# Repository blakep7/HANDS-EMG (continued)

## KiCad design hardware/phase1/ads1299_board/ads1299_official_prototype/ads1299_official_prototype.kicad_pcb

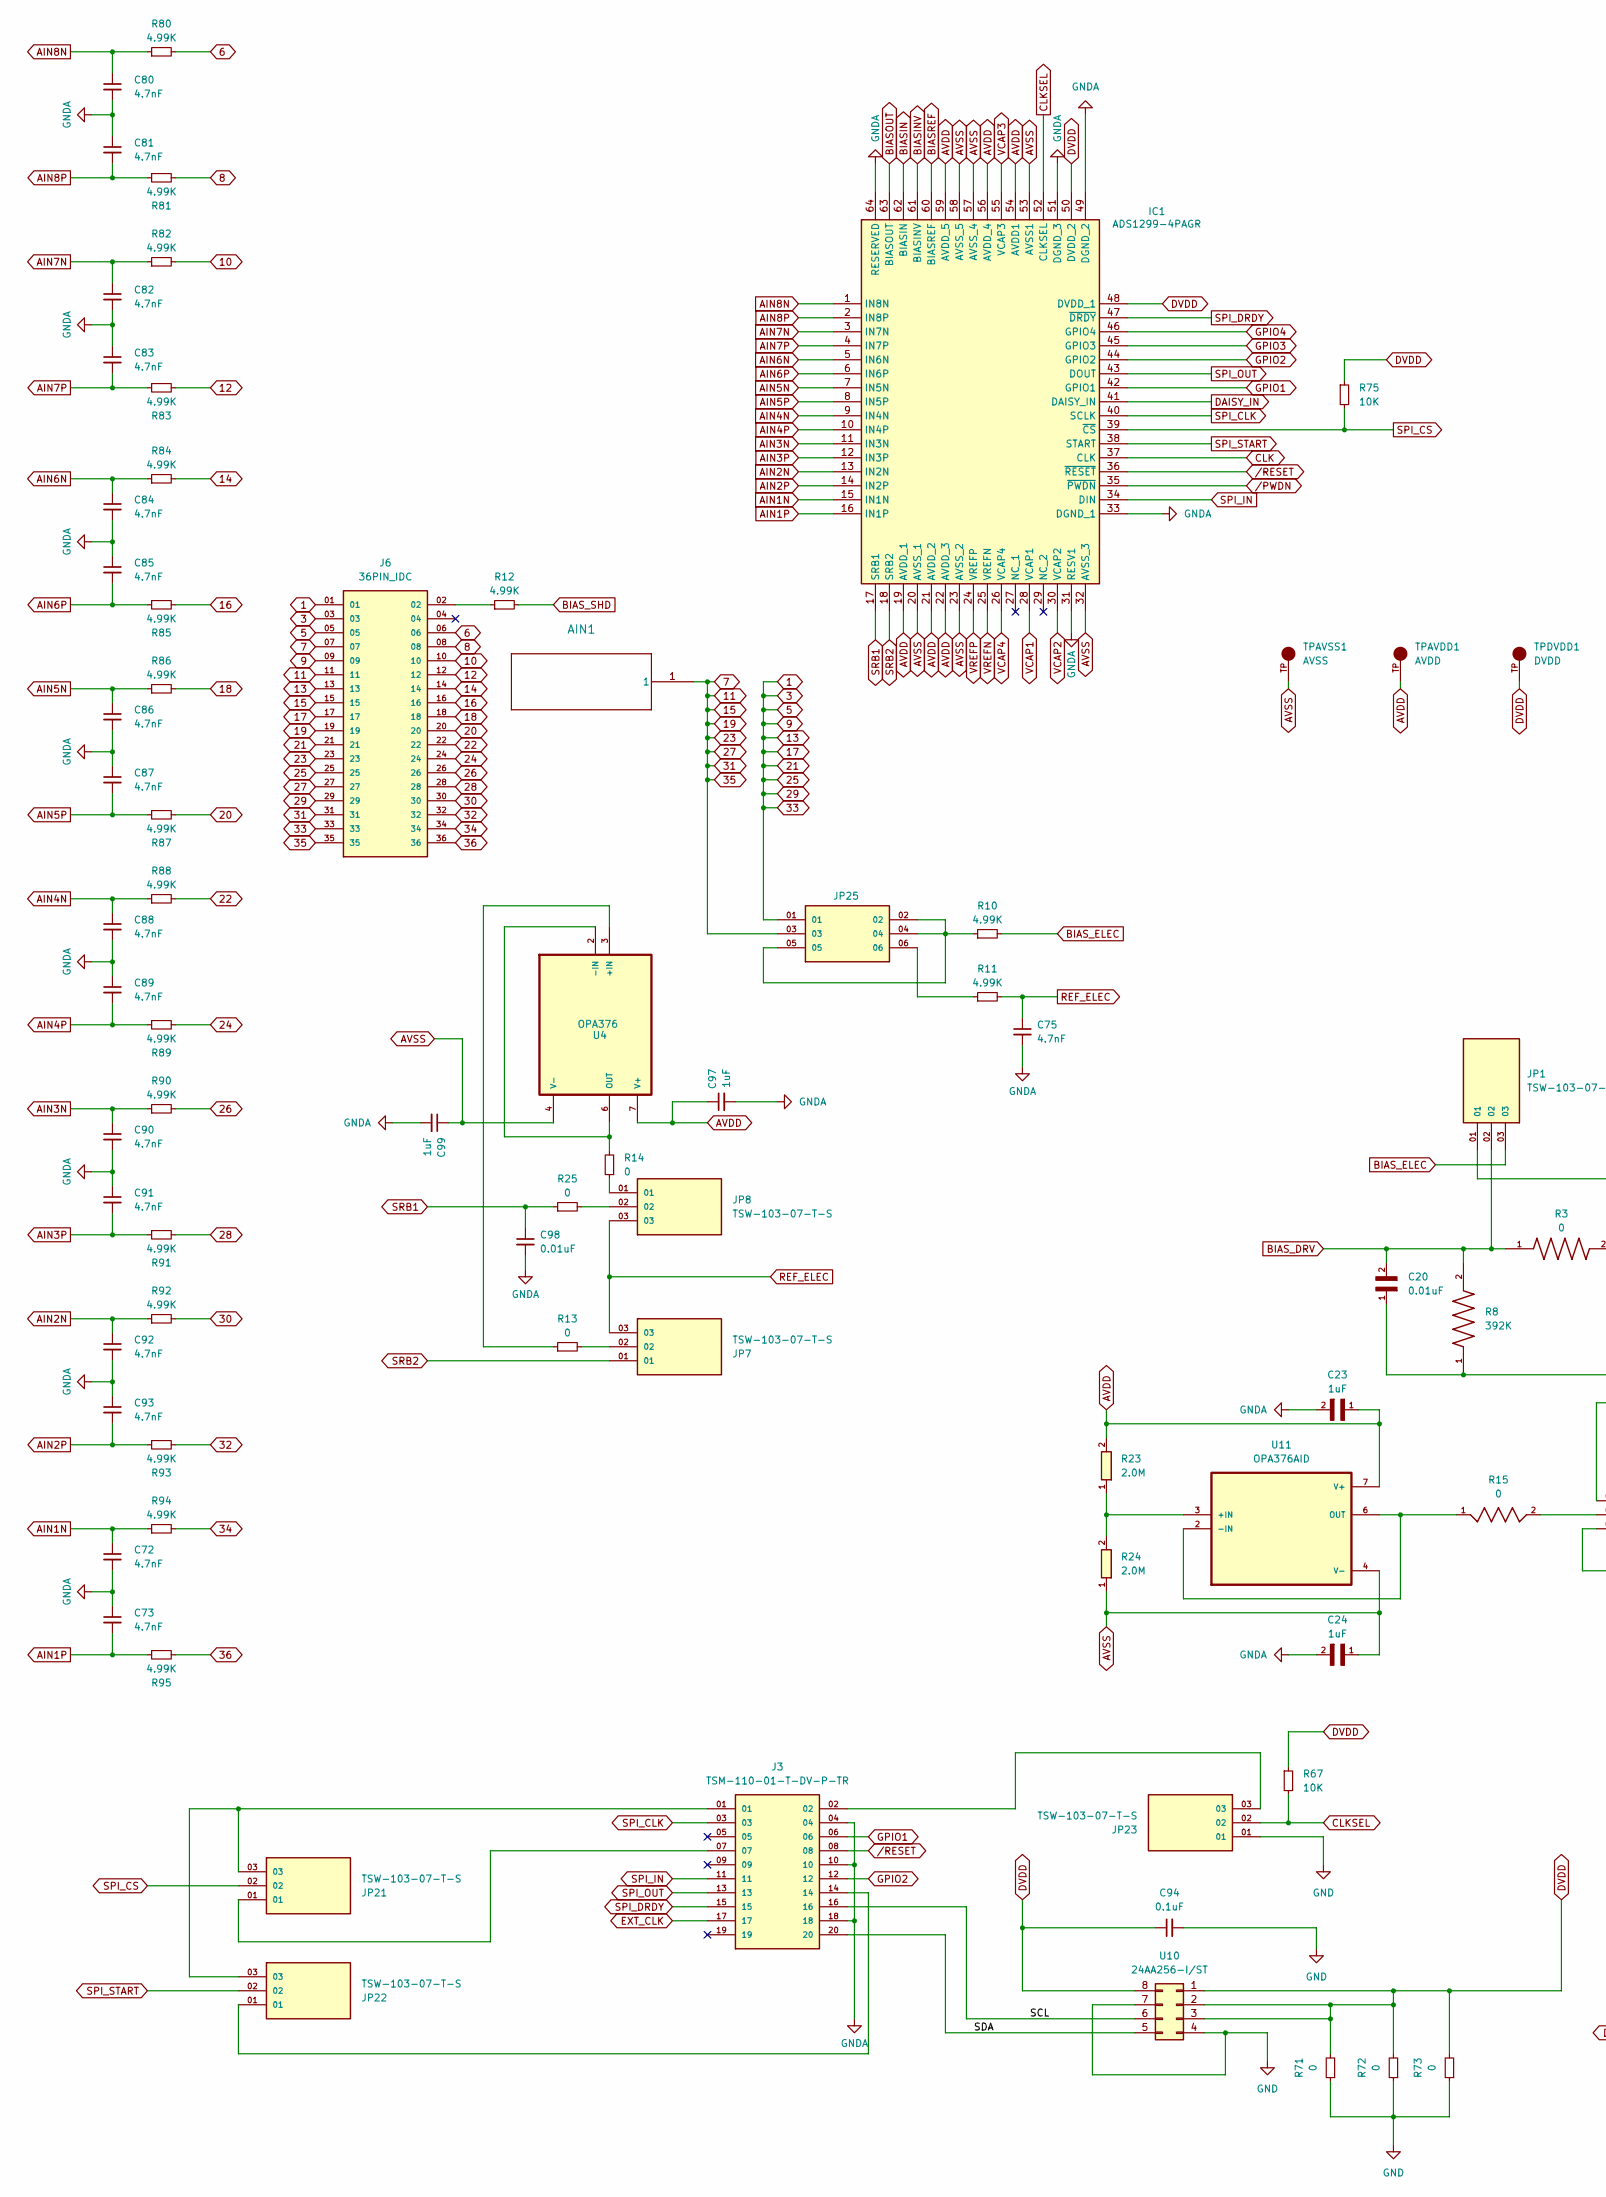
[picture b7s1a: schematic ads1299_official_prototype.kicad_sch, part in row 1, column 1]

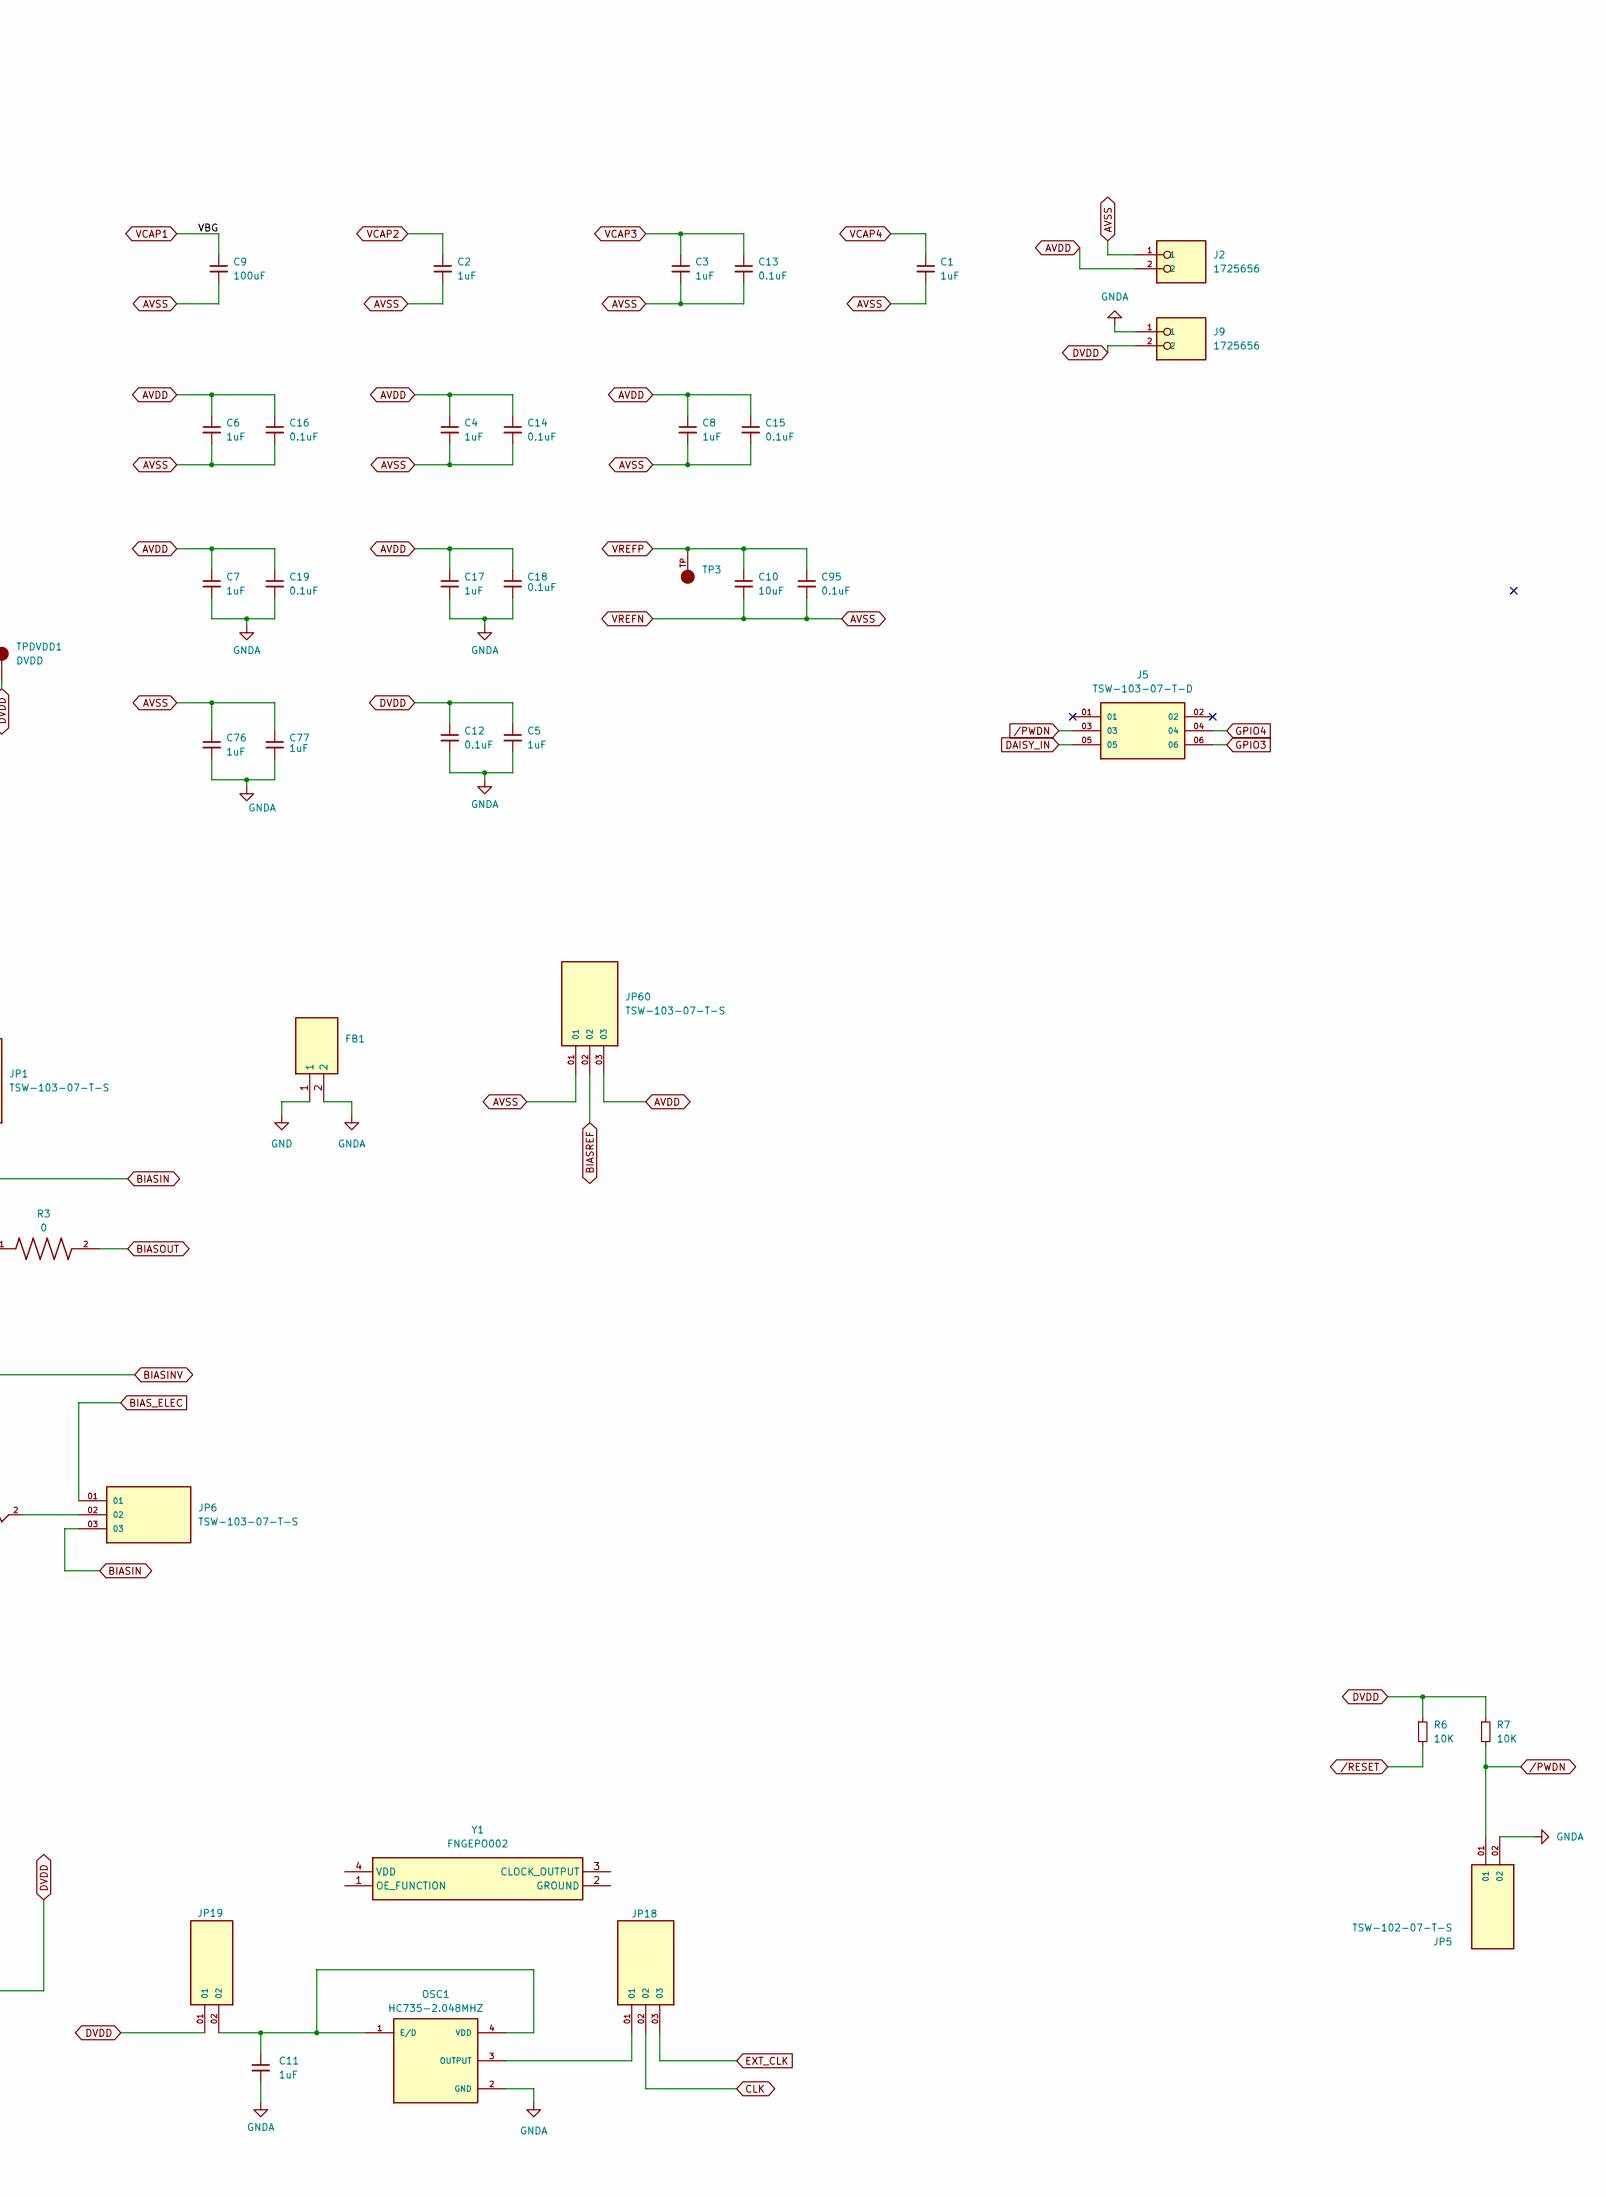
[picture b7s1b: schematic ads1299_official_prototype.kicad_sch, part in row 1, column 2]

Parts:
AIN1: AIN1; 132134_AMP
C1, C2, C3, C4, C5, C6, C7, C8, C11, C17, C23, C24, C76, C77, C97, C99: 1uF; CAPC1608X90N
C9: 100uF; CAPC3225X280N
C10: 10uF; CAPC2012X95N
C12, C13, C14, C15, C16, C18, C19, C94, C95: 0.1uF; CAPC1608X90N
C20, C98: 0.01uF; CAPC1608X90N
C72, C73, C75, C80, C81, C82, C83, C84, C85, C86, C87, C88, C89, C90, C91, C92, C93: 4.7nF; CAPC1608X90N
FB1: FCM_1608KF-601T03; BEADC1608X95N; Manufacturer_Part_Number FCM 1608KF-601T03
IC1: ADS1299-4PAGR; QFP50P1200X1200X120-64N; Manufacturer_Part_Number ADS1299-4PAGR; Mouser Part Number 595-ADS1299-4PAGR
J2, J9: 1725656; PHOENIX_1725656; PARTREV 03.03.2021
J3: TSM-110-01-T-DV-P-TR; SAMTEC_TSM-110-01-T-DV-P-TR
J5: TSW-103-07-T-D; SAMTEC_TSW-103-07-T-D; PARTREV R
J6: 36PIN_IDC; SAMTEC_SSW-118-21-F-D; PARTREV R
JP1, JP6, JP7, JP8, JP18, JP21, JP22, JP23, JP60: TSW-103-07-T-S; SAMTEC_TSW-103-07-T-S; PARTREV R
JP5, JP19: TSW-102-07-T-S; SAMTEC_TSW-102-07-T-S; PARTREV R
JP25: TSW-103-07-T-D; SAMTEC_TSW-103-07-T-D; PARTREV R
OSC1: HC735-2.048MHZ; XTAL_FXO-HC735-8; PARTREV 11/28/2007
R3, R25: 0; RESC1607X60N
R6, R7, R67, R75: 10K; RESC1607X60N
R8: 392K; RESC1608X55N
R10, R11, R12, R80, R81, R82, R83, R84, R85, R86, R87, R88, R89, R90, R91, R92, R93, R94, R95: 4.99K; RESC1608X60N
R13, R14, R15, R71, R72, R73: 0; RESC1005X40
R23, R24: 2.0M; 0603
TP3: 5000; KEYSTONE_5000; PARTREV H
TPAVDD1: AVDD; KEYSTONE_5000; PARTREV H
TPAVSS1: AVSS; KEYSTONE_5000; PARTREV H
TPDVDD1: DVDD; KEYSTONE_5000; PARTREV H
U4: OPA376; SOIC127P599X175-8N
U10: 24AA256-I/ST; SOP8P65_300X640X120L60X24N
U11: OPA376AID; SOIC127P599X175-8N
Y1: FNGEPO002; Manufacturer_Part_Number FNGEPO002; Mouser Part Number 729-FNGEPO002

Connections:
1: J6.01, J6.03, J6.05, J6.09, J6.13, J6.17, J6.21, J6.25, J6.29, J6.33, JP25.01
6: J6.06, R80.2
8: J6.08, R81.2
10: J6.10, R82.2
11: AIN1.1, J6.07, J6.11, J6.15, J6.19, J6.23, J6.27, J6.31, J6.35, JP25.03
12: J6.12, R83.2
14: J6.14, R84.2
16: J6.16, R85.2
18: J6.18, R86.2
20: J6.20, R87.2
22: J6.22, R88.2
24: J6.24, R89.2
26: J6.26, R90.2
28: J6.28, R91.2
30: J6.30, R92.2
32: J6.32, R93.2
34: J6.34, R94.2
36: J6.36, R95.2
/SCL: J3.16, U10.6
/SDA: J3.20, U10.5
AIN1N: C72.1, IC1.15 (IN1N), R94.1
AIN1P: C73.2, IC1.16 (IN1P), R95.1
AIN2N: C92.1, IC1.13 (IN2N), R92.1
AIN2P: C93.2, IC1.14 (IN2P), R93.1
AIN3N: C90.1, IC1.11 (IN3N), R90.1
AIN3P: C91.2, IC1.12 (IN3P), R91.1
AIN4N: C88.1, IC1.9 (IN4N), R88.1
AIN4P: C89.2, IC1.10 (IN4P), R89.1
AIN5N: C86.1, IC1.7 (IN5N), R86.1
AIN5P: C87.2, IC1.8 (IN5P), R87.1
AIN6N: C84.1, IC1.5 (IN6N), R84.1
AIN6P: C85.2, IC1.6 (IN6P), R85.1
AIN7N: C82.1, IC1.3 (IN7N), R82.1
AIN7P: C83.2, IC1.4 (IN7P), R83.1
AIN8N: C80.1, IC1.1 (IN8N), R80.1
AIN8P: C81.2, IC1.2 (IN8P), R81.1
AVDD: C4.1, C6.1, C7.1, C8.1, C14.1, C15.1, C16.1, C17.1, C18.1, C19.1, C23.1, C97.1, IC1.19 (AVDD_1), IC1.21 (AVDD_2), IC1.22 (AVDD_3), IC1.54 (AVDD1), IC1.56 (AVDD_4), IC1.59 (AVDD_5), J2.2, JP60.03, R23.2, TPAVDD1.TP, U4.7 (V+), U11.7 (V+)
AVSS: C1.2, C2.2, C3.2, C4.2, C6.2, C8.2, C9.2, C10.2, C13.2, C14.2, C15.2, C16.2, C24.1, C76.1, C77.1, C95.2, C99.1, IC1.20 (AVSS_1), IC1.23 (AVSS_2), IC1.25 (VREFN), IC1.32 (AVSS_3), IC1.53 (AVSS1), IC1.57 (AVSS_4), IC1.58 (AVSS_5), J2.1, JP60.01, R24.1, TPAVSS1.TP, U4.4 (V-), U11.4 (V-)
BIASIN: IC1.62 (BIASIN), JP1.01, JP6.03
BIASINV: C20.1, IC1.61 (BIASINV), R8.1
BIASOUT: IC1.63 (BIASOUT), R3.2
BIASREF: IC1.60 (BIASREF), JP60.02
BIAS_DRV: C20.2, JP1.02, R3.1, R8.2
BIAS_ELEC: JP1.03, JP6.01, R10.2
BIAS_SHD: R12.2
CLK: IC1.37 (CLK), JP18.02
CLKSEL: IC1.52 (CLKSEL), JP23.02, R67.2
DAISY_IN: IC1.41 (DAISY_IN), J5.05
DVDD: C5.1, C12.1, C94.1, IC1.48 (DVDD_1), IC1.50 (DVDD_2), J9.2, JP19.01, R6.1, R7.1, R67.1, R71.2, R72.2, R73.2, R75.1, TPDVDD1.TP, U10.1, U10.2, U10.3, U10.8
EXT_CLK: J3.17, JP18.03
GND: C94.2, FB1.1, JP23.01, R71.1, R72.1, R73.1, U10.4, U10.7
GNDA: C5.2, C7.2, C11.2, C12.2, C17.2, C18.2, C19.2, C23.2, C24.2, C72.2, C73.1, C75.2, C76.2, C77.2, C80.2, C81.1, C82.2, C83.1, C84.2, C85.1, C86.2, C87.1, C88.2, C89.1, C90.2, C91.1, C92.2, C93.1, C97.2, C98.2, C99.2, FB1.2, IC1.31 (RESV1), IC1.33 (DGND_1), IC1.49 (DGND_2), IC1.51 (DGND_3), IC1.64 (RESERVED), J3.04, J3.10, J3.18, J9.1, JP5.02, OSC1.2 (GND); also elsewhere on the board
GPIO1: IC1.42 (GPIO1), J3.06
GPIO2: IC1.44 (GPIO2), J3.12
GPIO3: IC1.45 (GPIO3), J5.06
GPIO4: IC1.46 (GPIO4), J5.04
unnamed: J3.01, JP21.03, JP22.03
unnamed: J3.02, JP23.03
unnamed: J3.07, JP21.01
unnamed: J3.14, JP22.01
unnamed: J6.02, R12.1
unnamed: JP6.02, R15.2
unnamed: JP7.02, R13.2
unnamed: JP8.01, R14.1
unnamed: JP8.02, R25.2
unnamed: JP25.02, JP25.04, JP25.05, R10.1
unnamed: JP25.06, R11.1
unnamed: C11.1, JP19.02, OSC1.1 (E/D), OSC1.4 (VDD)
unnamed: JP18.01, OSC1.3 (OUTPUT)
unnamed: R13.1, U4.3 (+IN)
unnamed: R14.2, U4.2 (-IN), U4.6 (OUT)
unnamed: R23.1, R24.2, U11.3 (+IN)
unnamed: R15.1, U11.2 (-IN), U11.6 (OUT)
REF_ELEC: C75.1, JP7.03, JP8.03, R11.2
SPI_CLK: IC1.40 (SCLK), J3.03
SPI_CS: IC1.39 (~CS), JP21.02, R75.2
SPI_DRDY: IC1.47 (~DRDY), J3.15
SPI_IN: IC1.34 (DIN), J3.11
SPI_OUT: IC1.43 (DOUT), J3.13
SPI_START: IC1.38 (START), JP22.02
SRB1: C98.1, IC1.17 (SRB1), R25.1
SRB2: IC1.18 (SRB2), JP7.01
VCAP1: C9.1, IC1.28 (VCAP1)
VCAP2: C2.1, IC1.30 (VCAP2)
VCAP3: C3.1, C13.1, IC1.55 (VCAP3)
VCAP4: C1.1, IC1.26 (VCAP4)
VREFP: C10.1, C95.1, IC1.24 (VREFP), TP3.TP
/PWDN: IC1.35 (~PWDN), J5.03, JP5.01, R7.2
/RESET: IC1.36 (~RESET), J3.08, R6.2

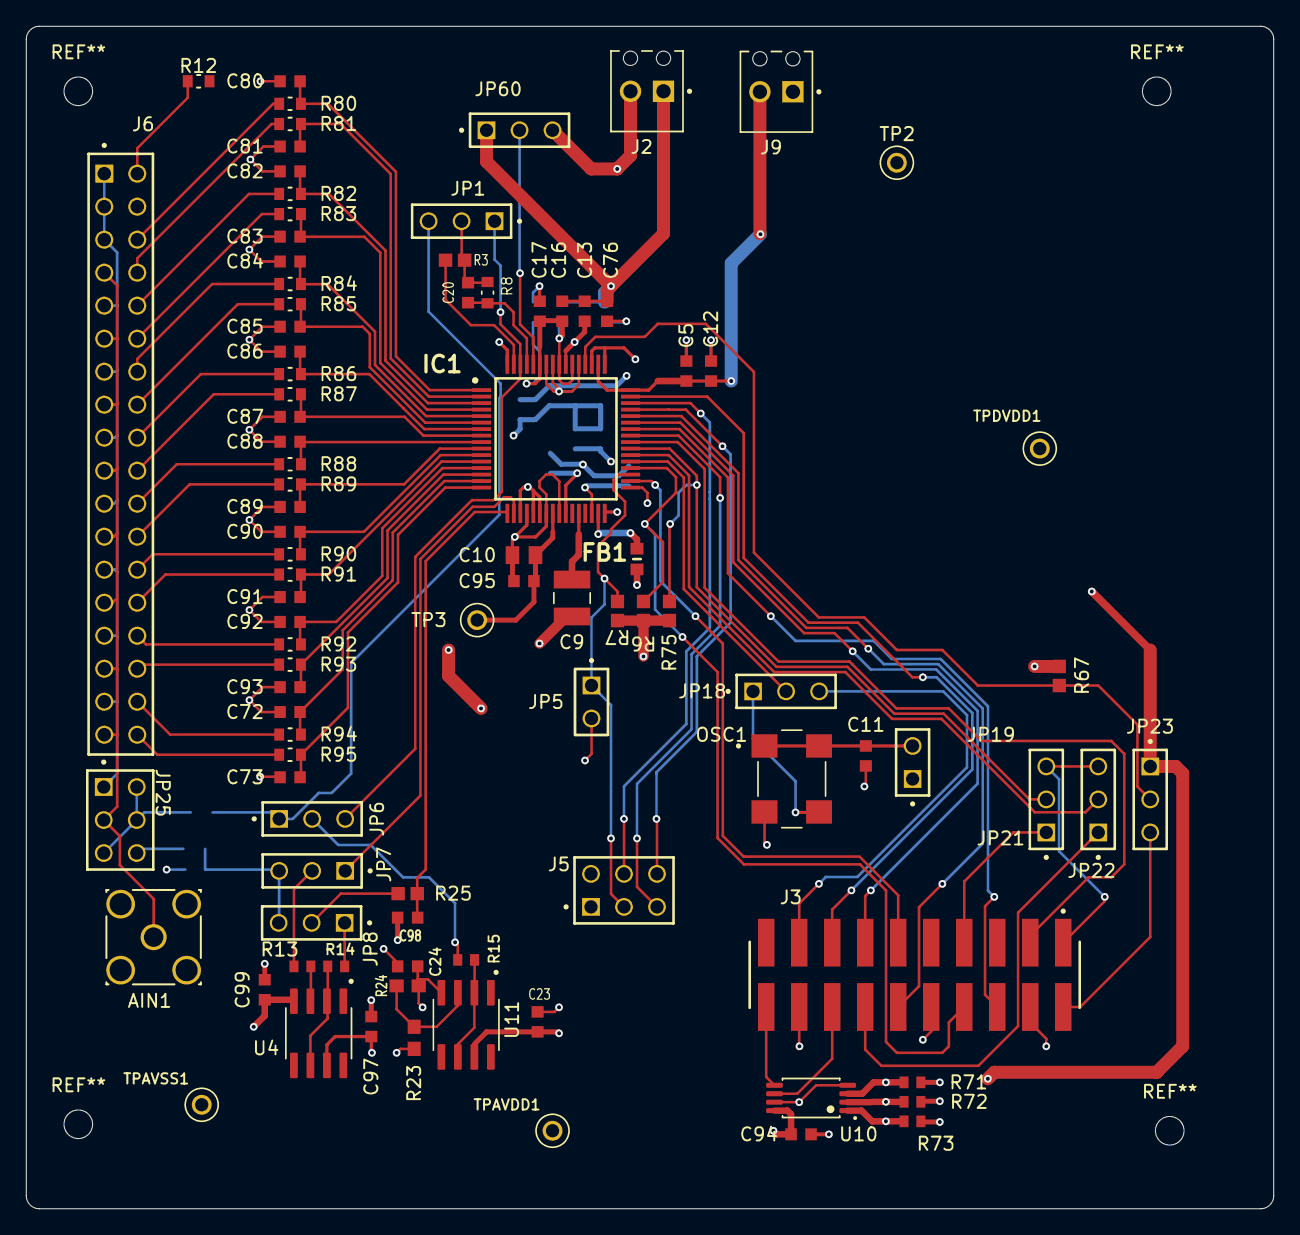
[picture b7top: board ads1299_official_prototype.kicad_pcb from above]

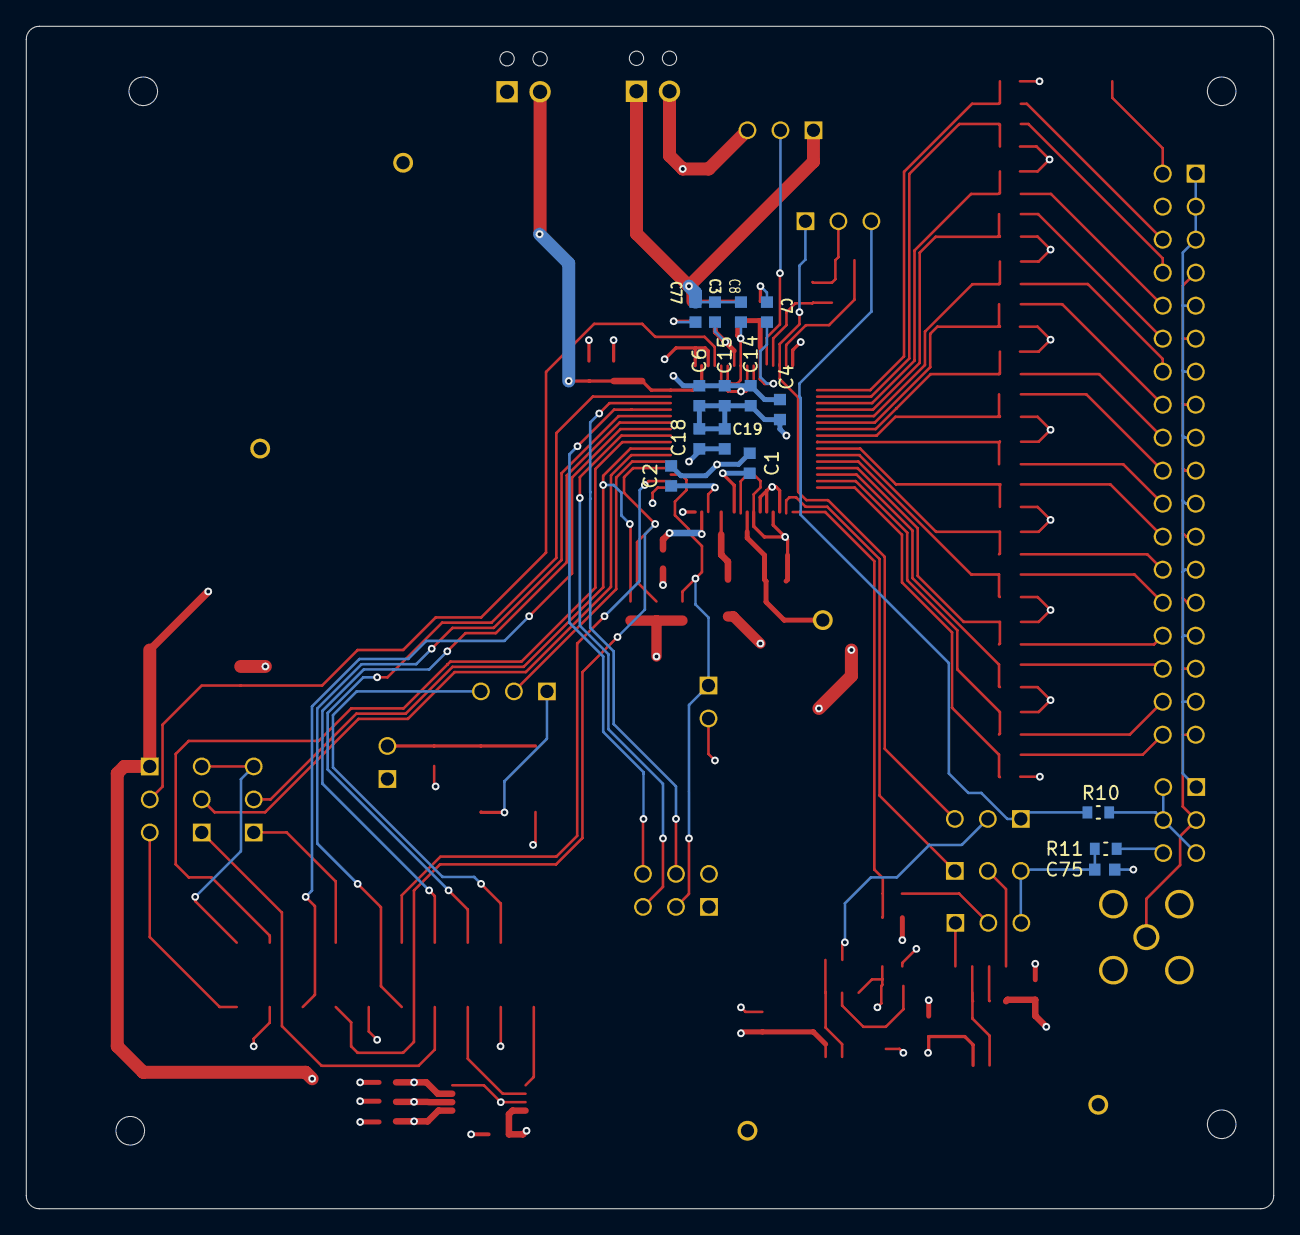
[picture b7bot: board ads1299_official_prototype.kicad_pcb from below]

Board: 4 copper layers, 96.0 x 91.0 mm, 109 parts (15 on the bottom side), 88 nets.

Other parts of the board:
TP2: 5001; KEYSTONE_5001

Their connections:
GNDA: TP2.TP; also elsewhere on the board

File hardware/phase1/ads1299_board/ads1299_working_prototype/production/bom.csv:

Designator,Footprint,Quantity,Value,LCSC Part #
AIN1,132134_AMP,1,AIN1,
"C1, C11, C17, C2, C23, C24, C3, C4, C5, C6, C7, C76, C77, C8, C97, C99",CAPC1608X90N,16,1uF,
C10,CAPC2012X95N,1,10uF,
"C12, C13, C14, C15, C16, C18, C19, C94, C95",CAPC1608X90N,9,0.1uF,
"C20, C98",CAPC1608X90N,2,0.01uF,
"C72, C73, C75, C80, C81, C82, C83, C84, C85, C86, C87, C88, C89, C90, C91, C92, C93",CAPC1608X90N,17,4.7nF,
C9,CAPC3225X280N,1,100uF,
FB1,BEADC1608X95N,1,FCM_1608KF-601T03,
IC1,QFP50P1200X1200X120-64N,1,ADS1299-4PAGR,
"J2, J9",PHOENIX_1725656,2,1725656,
J3,SAMTEC_TSM-110-01-T-DV-P-TR,1,TSM-110-01-T-DV-P-TR,
"J5, JP25",SAMTEC_TSW-103-07-T-D,2,TSW-103-07-T-D,
J6,SAMTEC_SSW-118-21-F-D,1,36PIN_IDC,
"JP1, JP18, JP21, JP22, JP23, JP6, JP60, JP7, JP8",SAMTEC_TSW-103-07-T-S,9,TSW-103-07-T-S,
"JP19, JP5",SAMTEC_TSW-102-07-T-S,2,TSW-102-07-T-S,
OSC1,XTAL_FXO-HC735-8,1,HC735-2.048MHZ,
"R10, R11, R12, R80, R81, R82, R83, R84, R85, R86, R87, R88, R89, R90, R91, R92, R93, R94, R95",RESC1608X60N,19,4.99K,
"R13, R14, R15, R71, R72, R73",RESC1005X40,6,0,
"R23, R24",0603,2,0,
"R25, R3",RESC1607X60N,2,0,
"R6, R67, R7, R75",RESC1607X60N,4,10K,
R8,RESC1608X55N,1,392K,
TP2,KEYSTONE_5001,1,5001,
TP3,KEYSTONE_5000,1,5000,
TPAVDD1,KEYSTONE_5000,1,AVDD,
TPAVSS1,KEYSTONE_5000,1,AVSS,
TPDVDD1,KEYSTONE_5000,1,DVDD,
U10,SOP8P65_300X640X120L60X24N,1,24AA256-I/ST,
U11,SOIC127P599X175-8N,1,OPA376AID,
U4,SOIC127P599X175-8N,1,OPA376,

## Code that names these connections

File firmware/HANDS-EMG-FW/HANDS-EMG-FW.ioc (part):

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Mcu.Name=STM32L496R(E-G)Tx
Mcu.Package=LQFP64
Mcu.UserName=STM32L496RGTx
PA0.Signal=GPIO_Analog
PA1.Mode=Full_Duplex_Master
PA1.Signal=SPI1_SCK
PA10.Signal=GPIO_Analog
PA11.Signal=GPIO_Analog
PA12.Signal=GPIO_Analog
PA13\ (JTMS/SWDIO).Mode=Serial_Wire
PA13\ (JTMS/SWDIO).Signal=SYS_JTMS-SWDIO
PA14\ (JTCK/SWCLK).Mode=Serial_Wire
PA14\ (JTCK/SWCLK).Signal=SYS_JTCK-SWCLK
PA15\ (JTDI).Signal=GPIO_Analog
PA2.Mode=Asynchronous
PA2.Signal=USART2_TX
PA3.Mode=Asynchronous
PA3.Signal=USART2_RX
PA4.GPIOParameters=GPIO_Label
PA4.GPIO_Label=SPI1_CS
PA4.Signal=GPIO_Output
PA5.GPIOParameters=GPIO_Label,GPIO_ModeDefaultEXTI
PA5.GPIO_Label=ADS1299_NDRDY
PA5.GPIO_ModeDefaultEXTI=GPIO_MODE_IT_FALLING
PA5.Signal=GPXTI5
PA6.Mode=Full_Duplex_Master
PA6.Signal=SPI1_MISO
PA7.Mode=Full_Duplex_Master
PA7.Signal=SPI1_MOSI
PA8.Signal=GPIO_Analog
PA9.Signal=GPIO_Analog
PB0.GPIOParameters=GPIO_Label
PB0.GPIO_Label=ADS1299_START
PB0.Signal=GPIO_Output
PB1.Signal=GPIO_Analog
PB10.Signal=GPIO_Analog
PB11.Signal=GPIO_Analog
PB12.Signal=GPIO_Analog
PB13.Signal=GPIO_Analog
PB14.Signal=GPIO_Analog
PB15.Signal=GPIO_Analog
PB2.Signal=GPIO_Analog
PB3\ (JTDO/TRACESWO).Signal=SYS_JTDO-SWO
PB4\ (NJTRST).Signal=GPIO_Analog
PB5.Signal=GPIO_Analog
PB6.Signal=GPIO_Analog
PB7.Signal=GPIO_Analog
PB8.Signal=GPIO_Analog
PB9.Signal=GPIO_Analog
PC0.Signal=GPIO_Analog
PC1.Signal=GPIO_Analog
PC10.Signal=GPIO_Analog
PC11.Signal=GPIO_Analog
PC12.Signal=GPIO_Analog
PC13.Signal=GPIO_Analog
PC14-OSC32_IN\ (PC14).Signal=GPIO_Analog
PC15-OSC32_OUT\ (PC15).Signal=GPIO_Analog
PC2.Signal=GPIO_Analog
PC3.Signal=GPIO_Analog
PC4.GPIOParameters=GPIO_Label
PC4.GPIO_Label=ADS1299_NPWDN
PC4.Signal=GPIO_Output
PC5.GPIOParameters=GPIO_Label
PC5.GPIO_Label=ADS1299_NRESET
PC5.Signal=GPIO_Output
PC6.Signal=GPIO_Analog
PC7.Signal=GPIO_Analog
PC8.Signal=GPIO_Analog
PC9.Signal=GPIO_Analog
PD2.Signal=GPIO_Analog
PH0-OSC_IN\ (PH0).Signal=GPIO_Analog
PH1-OSC_OUT\ (PH1).Signal=GPIO_Analog
PH3-BOOT0.Signal=GPIO_Analog
RCC.HSE_VALUE=8000000
RCC.SYSCLKFreq_VALUE=80000000
RCC.SYSCLKSource=RCC_SYSCLKSOURCE_PLLCLK
board=custom

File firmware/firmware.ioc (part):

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Mcu.Name=STM32L496Z(E-G)Tx
Mcu.Package=LQFP144
Mcu.UserName=STM32L496ZGTx
PA1.Mode=Full_Duplex_Master
PA1.Signal=SPI1_SCK
PA10.Mode=Asynchronous
PA10.Signal=USART1_RX
PA11.Mode=Device_Only
PA11.Signal=USB_OTG_FS_DM
PA12.Mode=Device_Only
PA12.Signal=USB_OTG_FS_DP
PA6.Mode=Full_Duplex_Master
PA6.Signal=SPI1_MISO
PA7.Mode=Full_Duplex_Master
PA7.Signal=SPI1_MOSI
PA9.Mode=Asynchronous
PA9.Signal=USART1_TX
PG13.Mode=I2C
PG13.Signal=I2C1_SDA
PG14.Mode=I2C
PG14.Signal=I2C1_SCL
RCC.HSE_VALUE=8000000
RCC.SYSCLKFreq_VALUE=80000000
RCC.SYSCLKSource=RCC_SYSCLKSOURCE_PLLCLK
board=custom

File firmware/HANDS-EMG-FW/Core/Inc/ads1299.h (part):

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 */
#define ADS1299_DEFAULT_REG_ID			    ADS1299_4_DEVICE_ID
#define ADS1299_DEFAULT_REG_CONFIG1		    0x96					// Daisy chain disabled, Int OSC output disabled, Data Rate = 250Hz (Fmod/4096)
#define ADS1299_DEFAULT_REG_CONFIG2		    0xC0					// Text source driven externally, Signal amplitude 1*-(VREFP-VREFN)/2400, Frequency pulsed at fclk/2^21
#define ADS1299_DEFAULT_REG_CONFIG3		    0x60					// Power down internal ref buffer, Bias open, BiasRef fed externally, Bias buff powered down, Bias sense disabled, Bias connected
#define ADS1299_DEFAULT_REG_LOFF		    0x00					// Lead off comparitor threashold 95% for pos - 5% for neg, Current magnitude for lead off 6nA, Lead-Off in DC detection
#define ADS1299_DEFAULT_REG_CHNSET		    0x61					// Normal operation, Gain 24x, SRB2 Open, Channel input is shorted for offset/noise measurement
#define ADS1299_DEFAULT_REG_BIAS_SENSP	    0x00					// INxP to BIAS disabled for xE{1,2,3,4,5,6,7,8}
#define ADS1299_DEFAULT_REG_BIAS_SENSN	    0x00					// INxN to BIAS disabled for xE{1,2,3,4,5,6,7,8}
#define ADS1299_DEFAULT_REG_LOFF_SENSP	    0x00					// INxP Lead off detection disabled for xE{1,2,3,4,5,6,7,8}
#define ADS1299_DEFAULT_REG_LOFF_SENSN	    0x00					// INxN lead off detection disabled for xE{1,2,3,4,5,6,7,8}
#define ADS1299_DEFAULT_REG_LOFF_FLIP	    0x00					// Chx lead off polarity flip set to no flip for xE{1,2,3,4,5,6,7,8}
#define ADS1299_DEFAULT_REG_LOFF_STATP	    0x00					// Chx positive lead off status (0: electrode off, 1: electrode on) ignored
#define ADS1299_DEAFULT_REG_LOFF_STATN	    0x00					// Chx negative lead off status ''
#define ADS1299_DEFAULT_REG_GPIO		    0x0F					// All GPIO pins set to input
#define ADS1299_DEFAULT_REG_MISC1		    0x00                    // SRB1 (Stimulus, refrence, and bias 1) connect to all channels inverting inputs
#define ADS1299_DEFAULT_REG_MISC2		    0x00                    // Always read 0 RESERVED
#define ADS1299_DEFAULT_REG_CONFIG4		    0x00                    // Continuous conversion mode enabled, lead off comparitors disabled

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#define	ADS1299_ADDRESS_REG_ID			 0x00			// Chip ID register. Read-only. ID[4:0] should be ADS1299_4_DEVICE_ID.
#define	ADS1299_ADDRESS_REG_CONFIG1		 0x01			// Configuration register 1. Controls daisy-chain mode; clock output; and data rate.
#define	ADS1299_ADDRESS_REG_CONFIG2		 0x02			// Configuration register 2. Controls calibration signal source, amplitude, and frequency.
#define	ADS1299_ADDRESS_REG_CONFIG3		 0x03			// Configuration register 3. Controls reference buffer power and the bias functionality.
#define	ADS1299_ADDRESS_REG_LOFF		 0x04			// Lead-off control register. Controls lead-off frequency, magnitude, and threshold.
#define	ADS1299_ADDRESS_REG_CH1SET		 0x05			// Channel 1 settings register. Controls channel 1 input mux, SRB2 switch, gain, and power-down.
#define	ADS1299_ADDRESS_REG_CH2SET		 0x06			// Channel 2 settings register. Controls channel 2 input mux, SRB2 switch, gain, and power-down.
#define	ADS1299_ADDRESS_REG_CH3SET		 0x07			// Channel 3 settings register. Controls channel 3 input mux, SRB2 switch, gain, and power-down.
#define	ADS1299_ADDRESS_REG_CH4SET		 0x08			// Channel 4 settings register. Controls channel 4 input mux, SRB2 switch, gain, and power-down.
#define	ADS1299_ADDRESS_REG_CH5SET		 0x09			// Channel 5 settings register. Controls channel 5 input mux, SRB2 switch, gain, and power-down.
#define	ADS1299_ADDRESS_REG_CH6SET		 0x0A			// Channel 6 settings register. Controls channel 6 input mux, SRB2 switch, gain, and power-down.
#define	ADS1299_ADDRESS_REG_CH7SET		 0x0B			// Channel 7 settings register. Controls channel 7 input mux, SRB2 switch, gain, and power-down.
#define	ADS1299_ADDRESS_REG_CH8SET		 0x0C			// Channel 8 settings register. Controls channel 8 input mux, SRB2 switch, gain, and power-down.
#define	ADS1299_ADDRESS_REG_BIAS_SENSP	 0x0D			// Bias drive positive sense selection. Selects channels for bias drive derivation (positive side).
#define	ADS1299_ADDRESS_REG_BIAS_SENSN	 0x0E			// Bias drive negative sense selection. Selects channels for bias drive derivation (negative side).
#define	ADS1299_ADDRESS_REG_LOFF_SENSP	 0x0F			// Lead-off positive sense selection. Selects channels that will use lead-off detection (positive side).
#define	ADS1299_ADDRESS_REG_LOFF_SENSN	 0x10			// Lead-off negative sense selection. Selects channels that will use lead-off detection (negative side).
#define	ADS1299_ADDRESS_REG_LOFF_FLIP	 0x11			// 1: Swaps lead-off current source and sink on the corresponding channel. See datasheet.
#define	ADS1299_ADDRESS_REG_LOFF_STATP	 0x12			// Lead-off positive side status register. Read-only. 0: lead on, 1: lead off.
#define	ADS1299_ADDRESS_REG_LOFF_STATN	 0x13			// Lead-off negative side status register. Read-only. 0: lead on, 1: lead off.
#define	ADS1299_ADDRESS_REG_GPIO		 0x14			// GPIO register. Controls state and direction of the ADS1299 GPIO pins.
#define	ADS1299_ADDRESS_REG_MISC1		 0x15			// Miscellaneous 1. Connects/disconnects SRB1 to all channels' inverting inputs.
#define	ADS1299_ADDRESS_REG_MISC2		 0x16			// Miscellaneous 2. No functionality in current revision of ADS1299.
#define	ADS1299_ADDRESS_REG_CONFIG4		 0x17			// Configuration register 4. Enables/disables single-shot mode and controls lead-off comparator power.

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/**
 *  @brief Bit mask definitions for CONFIG2.CAL_AMP0 (calibration signal amplitude).
 */
#define	ADS1299_REG_CONFIG2_CAL_AMP_VREF_DIV_2_4_MV		(0<<2)		// Calibration signal amplitude is 1 x (VREFP - VREFN)/(2.4 mV).
#define	ADS1299_REG_CONFIG2_CAL_AMP_2VREF_DIV_2_4_MV	(1<<2)		// Calibration signal amplitude is 2 x (VREFP - VREFN)/(2.4 mV).

/**
 *  @brief Bit mask definitions for CONFIG2.INT_CAL (calibration signal source).
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#define	ADS1299_REG_CONFIG3_REFBUF_ENABLED			(1<<7)

/**
 *  @brief Bit mask definitions for CONFIG3.BIAS_MEAS (enable or disable bias measurement through BIASIN pin).
 */
#define	ADS1299_REG_CONFIG3_BIAS_MEAS_DISABLED			(0<<4)
#define	ADS1299_REG_CONFIG3_BIAS_MEAS_ENABLED			(1<<4)
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#define	ADS1299_REG_CHNSET_GAIN_24				(6<<4)			// PGA gain = 24.

/**
 *  @brief Bit mask definitions for CHnSET.SRB2 (channel internal connection to SRB2 pin).
 */
#define	ADS1299_REG_CHNSET_SRB2_DISCONNECTED	(0<<3)
#define	ADS1299_REG_CHNSET_SRB2_CONNECTED		(1<<3)
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 */
#define	ADS1299_REG_CHNSET_NORMAL_ELECTRODE		0			// Channel is connected to the corresponding positive and negative input pins.
#define	ADS1299_REG_CHNSET_INPUT_SHORTED		1			// Channel inputs are shorted together. Used for offset and noise measurements.
#define	ADS1299_REG_CHNSET_BIAS_MEASUREMENT		2			// Used with CONFIG3.BIAS_MEAS for bias measurement. See ADS1299 datasheet, pp. 53-54.
#define	ADS1299_REG_CHNSET_MVDD_SUPPLY			3			// Used for measuring analog and digital supplies. See ADS1299 datasheet, p. 17.
#define	ADS1299_REG_CHNSET_TEMPERATURE_SENSOR	4			// Measures device temperature. See ADS1299 datasheet, p. 17.
#define	ADS1299_REG_CHNSET_TEST_SIGNAL			5			// Measures calibration signal. See ADS1299 datasheet, pp. 17 and 41.
#define	ADS1299_REG_CHNSET_BIAS_DRIVE_P			6			// Connects positive side of channel to bias drive output.
#define	ADS1299_REG_CHNSET_BIAS_DRIVE_N			7 			// Connects negative side of channel to bias drive output.

/**
 *  @brief Combined value of reserved bits in CHnSET registers.
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/**
 *  @brief Bit mask definitions for MISC1.SRB1 (SRB1 internal connection).
 */
#define	ADS1299_REG_MISC1_SRB1_OFF		(0<<5)			// Stim/ref/bias 1 turned off.
#define	ADS1299_REG_MISC1_SRB1_ON		(1<<5)			// Stim/ref/bias 1 connected to all channel inverting inputs.

/**
 *  @brief Combined value of reserved bits in MISC1 register.
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
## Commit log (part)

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2024-09-13 Add documentation folder
2024-09-25 Finalized Proposal Diagram
    Let me know what yall think
2024-09-26 Add BOM
2024-09-27 Changed name of block diagram, new high level system overview
2024-10-02 Updated Block Diagram to show ADS1299 as procured component
2024-10-04 Update design documentation, block diagrams
2024-10-05 Updated system overview to include elbow gnd
2024-10-08 Added a risk analysis .txt file
    Use this to self analyze the risk associated with your portion based on *actual research*, not conjecture about how hard it will be to make.
2024-10-09 Added my requirements notes
2024-10-14 changed some diagrams, and added others
    Added procedures for electrode placement
2024-10-15 Procedure With Pictures
2024-10-21 added QFN to DIP schem
    currently unfinished, needs compensator along boost rail, and also pin alignments for right side of pinout
2024-11-08 Delete Documentation/Design_Documentation/DATA_ACQUISITION_PROCEDURE_W:Pictures.docx
    Deleted Corrupted file that was preventing a push
2024-11-08 Added QFN to DIP schem.
    Currently just has LTC and USB on schema
2024-11-12 Add files via upload
    added zio connectors, based on STM32 eval kit
2024-11-13 this includes some basic data and scripts
    excludes subject 1, exercise 1 raw data... data size is too large to commit, maybe a drive link? zip?
    Introductory script for model in tensorflow
    custom matlab script for windowing the Ninapro data.
2024-11-13 added some more comments to improve readability
    added credit to the matlab script, as I got the windowing idea from an existing piece of literature
2024-11-14 Repo file restructure
2024-11-14 replaced ML destination to fit file structure
2024-11-17 PMIC LTC3556_Final version
    Please see attached LTC3556 pcb Schematic
2024-11-19 Create PGA_Config
2024-11-23 added some specific diagrams for blake
    front profile mechanical view plus a top down profile.
2024-11-23 Added ML Process Diagram
2025-01-07 Add files via upload
    I corrections for the ERC errors from 25 to 14 power flags. I will continue to correct PMIC layout this week. i will work on footprint also.
2025-01-08 Add files via upload
    I redrew PMIC schematic but there are still two errors. I do not believe I can tie Pins 1 and 24 together for the one error. The other error relates to Pin-10, which i will correct
2025-01-09 Add files via upload
    stm32 board 1/8/25
2025-01-10 Update stm32_official_prototype.kicad_sch
    organized into sub-blocks
2025-01-11 Update stm32_official_prototype.kicad_sch
    removed unnecessary circuitry
2025-01-11 stm32 board update (1.11.25)
    - correcting footprints (IP)
    - left off on USB circuitry
    - note: net labels must be corrected for differential pair
2025-01-14 stm32 pcb update for (1.13.25)
    - most components are now connected
    - need to verify a few more footprints
    - board is ~65% finished
2025-01-14 Add files via upload
    -ERC are completed
    -made corrections to pin 1 to pin 10 DVCC, to STM32_3V3
    -Will start footprint tomorrow
2025-01-15 ADS1299 progress (1.14.25)
    - finalizing ads1299 schematic
    - left off on power supply circuitry
2025-01-19 Add files via upload
    - Currently routing tracking high current inductors, for PMIC
    - Vout/ Input thither traces
2025-01-22 Add files via upload
    - Schematic 100% complete
    - LTC3556_PCB project design 95%
    - Need to edit trace thickness for Vout. Need you guys feedback and recommendation
2025-01-23 ads1299 PCB update (1.22.25)
    - left off on figuring out all the "Not Installed" footprints
    - some components may have the wrong designator
    - some components are missing footprints
2025-01-26 STM32 board update (1.25.25)
    - vastly improved the layout
    - verified ALL footprints
    - implemented correct JLCPCB design rules
    - left off on labeling
2025-01-27 Add files via upload
    - 98% completed
    - Need to fix minor touch on silkscreen layer
    -Started searching manufacture parts on data sheet
    0 finalizing Gerber file last
2025-01-28 Update documentation
2025-01-31 original gerber files provided by TI
    original gerber files provided by TI
    - open all these files at once in KiCad Gerber Viewer
    - shows the entire eval.kit layout that you can deconstruct layer by layer (not component by component)
2025-01-31 ads1299 update (1.30.25)
    - omit all NI components
    - i still think it is a good idea to expose all pins for now, so i left off on implementing "Figure 62. ECG MDK Board Interface Adapter"
2025-02-03 stm32 board update (2.2.25)
    all...144 pins...are wired.
    - still need to connect power circuitry to chip
    - still need to connect USB circuitry to chip
    - run by Mark Bruno tmrw --> order right away after
2025-02-05 ads1299 2nd update (2.5.25)
    - verified footprints
2025-02-05 Add files via upload
    -Added TC7660EOA charge pump for AFE -2.5V AVSS
    - Ppdated integration of both U1 and U2 IC's, V_Out I/O connections.
2025-02-07 Add files via upload
    - PMIC, LTC3556 and charge Pump, TC7660EOA 98% completed
    - Made corrections to 4-layer board, copper traces, via's grounds VOUT's vias corrections and ERC errors and warning corrections completed
    - Added -2.5V AFE output for AVSS via (charge pump)
    - will completed Gerber @ final step for JLCPCB
    - We have the option for JLCPCB to assemble board for us
2025-02-09 barrel jack update ads1299 (2.8.25)
    - schematic seems to be done
    - might have some power flag issues
    - many components require footprint assignments still, base those footprints off the ADS1299 BOM
2025-02-09 legit stm32 schematic (2.8.25)
    - removed most if not all redundant short breakers
    - implemented extra safeguard for temporary power supply
    - BOARD IS SUPPLIED THROUGH +3V3 pin 16 on connector CN11
2025-02-10 layout finish, clearing all DRC errors stm32 update (2.9.25)
2025-02-11 Added poor performance model file
    Poor performance model with 50% accuracy for upload verificaiton onto stm32
2025-02-11 Added model in .cc for embedded sys
2025-02-11 Add files via upload
    Please see the latest LTC3556v2.0 updated project file
2025-02-14 Add firmware project to git.
2025-02-14 Revert "Add firmware project to git."
    This reverts commit e69bf5e09d36e8360c9e7194ebd920edb41fe854.
2025-02-14 set config ignorecase to false
2025-02-14 Move readme back
2025-02-14 Rename Hardware -> hardware_temp, Firmware -> firmware_temp
2025-02-14 KiCad V6+ ADS1299 footprints
2025-02-14 fix duplicate directories
2025-02-14 move readme back to root
2025-02-14 fix hardware duplicate folder
2025-02-14 Add footprints zip that was lost during fixing
2025-02-17 ads1299 gerber files
2025-02-17 Add files via upload
    - Team still is the final PMIC: PCB layout, footprint
    - Schematic drawing
    -3D model-errors: zero
    -Read to create Gerber file
2025-02-19 Add files via upload
    Team: here is the final version files of PMIC: LTC3556 and TC7760EOA
    - Schematic diagram
    -PCB layout and 3D model
    - 4Layer PCB
    - Production Gerber files
    - cleaned up the placement for ADS1299, AFE and STM32 connection female pins
2025-02-19 ADS1299 Updated J3 and organized routes, speeding up placement and routing
2025-02-19 Update STM32 to unconnect uUSB shield from GND
2025-02-19 Add KiCad gitignore
2025-02-19 Remove excess files, add gitignore for OS files
2025-02-19 Renamed Hardware to hardware
2025-02-19 Update PMIC directory with KIRK'S changes
2025-02-20 Update LTC to add JLC MPNs and fix JST plug
2025-02-20 Update PMIC board: edit resistor values, added MPN numbers, fixed headers
2025-02-20 Add firmware project:
2025-02-22 final manufacturing version stm32 (2.21.25)
2025-02-22 Schematic changes, no more power stuff from external board. Layout work, added power stuff, lots to do
2025-02-23 "idk whats the final anymore" stm32 board (2.22.25)
2025-02-23 Merge branch 'main' of https://github.com/blakep7/Senior-Design-Team-9
    ADS1299 update, most traces done and power routed
2025-02-23 Update STM board
2025-02-23 Fix STM floating gnd
2025-02-24 Schematic and Layout updates
    Added Bias stuff, routing now and updates from Schematic to Layout working beautifully now. trying to figure out if the capacitors are currently hooked up correctly for AVSS and AVDD or if we need mo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
2025-02-25 Only thing left is the AVDD power routing, not sure if we can just connect that to power plane or not. Also ground plane, then done
2025-02-25 Planes are in, need to ask bruno on specifics about them then done
2025-02-26 Chat it's done
2025-02-26 configure STM project
2025-02-26 Okay done
2025-02-26 Update firmware project
2025-02-26 Only official prototype file, fully finalized with BOM
2025-02-27 Update mainModel.py
    python done
2025-02-27 SW side complete
    waiting on ninapro to download, then will package data for deployment
2025-02-28 Add firmware for STM32 with CubeAI enabled.
2025-03-01 Add final PCB directory, add final pcb schematic layout, add final pcb pcb layout, add final pcb custom kicad library
2025-03-01 Update sizes of schematics
2025-03-01 Silkscreen board, add USB connector
2025-03-01 dataset and feature extraction
2025-03-01 Fix LTC3556 projectfile
2025-03-01 Add interactive bom
2025-03-04 added feature extraction .c file
    needs to be interfaced with windowing function and state machine. Testing relegated to individual testing for now
2025-03-04 fixed features, added 1 more
2025-03-04 edited some additional background files
2025-03-07 added test bin file
2025-03-07 changed to hex representation
2025-03-07 add data array for testing hex
2025-03-11 Add new PMIC board version for phase 2 after bugs found in integration testing
2025-03-11 Update text on schematic
2025-03-11 Update power path track widths
2025-03-12 Add changes based on bruno's suggestions for thermal releif
2025-03-13 Add files via upload
    @Blake please see my updated version I have question about the net VOUT,VIN's network.
2025-03-21 use this as the final pcb project (blake suks lol)
2025-03-23 finalpcb update (3.23.25)
    schematic nearly done, need footprint assignments.
2025-03-24 half ads layout done (3.24.25)
2025-03-26 clean up main
2025-03-30 basic routing (3.30.25)
2025-03-31 added ltc3586 and ads1299 LDOs (3.31.25)
2025-04-02 final pcb update 4.2.25 (added dongle usb stuff)
2025-04-02 Added ECG portions to the final, corrected -5 points
2025-04-05 90% of components are placed (4.5.25)
    NEED TESTPOINTS and configure the jumper parts for the PMIC without using jumpers
2025-04-06 organized schematic, needs verification (4.6.25)
2025-04-06 fixed and organized schematic (4.6.25)
2025-04-08 Update firmware, add threshold based collection of ADS1299 data, working ML model on device
2025-04-09 Added software suite for edge device
2025-04-09 Update thresholding
2025-04-09 Power routed, not clean but in
2025-04-13 traces got fucked up so i rerouted pmic (4.13.25)
2025-04-16 basically done, everyone please verify if possible (4.16.25)
2025-04-16 lol forgot buttons (4.16.25)
2025-04-17 not all but most 3d models
2025-04-17 System Integration Test Report
2025-04-21 labeled battery (4.21.25)
2025-04-22 Add documentation for integration test report
2025-05-05 Update pcb with production files
2025-05-10 Finalizing project, adding final firmware, adding final PCB design
